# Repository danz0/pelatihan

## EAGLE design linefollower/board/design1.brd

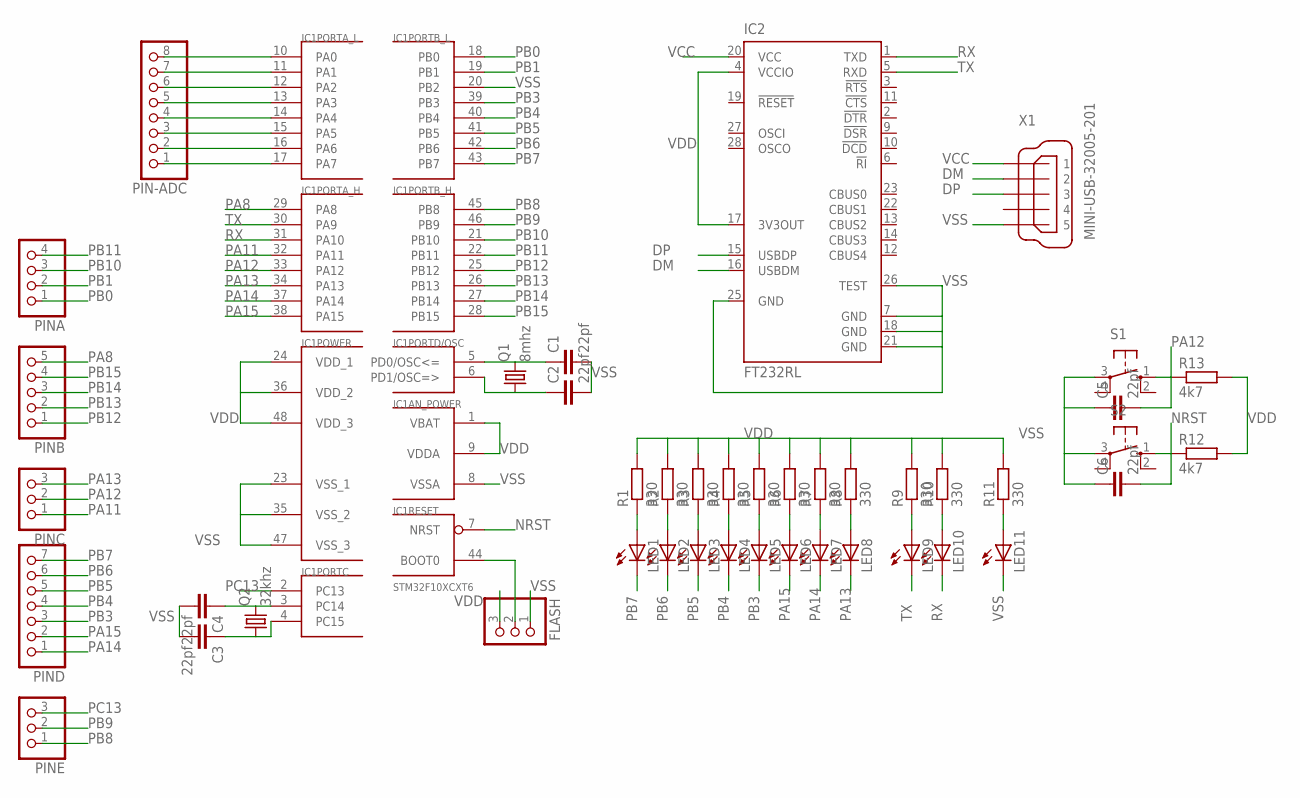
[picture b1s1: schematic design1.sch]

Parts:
C1, C2, C3, C4, C5, C6: 22pf; C1206
FLASH: PINHD-1X3; 1X03
IC1: STM32F10XCXT6; TQFP48
IC2: FT232RL; SSOP28
LED1, LED2, LED3, LED4, LED5, LED6, LED7, LED8, LED9, LED10, LED11: LEDSML1206; SML1206
PIN-ADC: PINHD-1X8; 1X08
PINA: PINHD-1X4; 1X04
PINB: PINHD-1X5; 1X05
PINC: PINHD-1X3; 1X03
PIND: PINHD-1X7; 1X07
PINE: PINHD-1X3; 1X03
Q1: 8mhz; HC49U-V
Q2: 32khz; TC26V
R1, R2, R3, R4, R5, R6, R7, R8, R9, R10, R11: 330; R1206
R12, R13: 4k7; R1206
S1, S2: 10-XX; B3F-10XX
X1: MINI-USB-32005-201; 32005-201

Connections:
ADC0: IC1.10 (PA0), PIN-ADC.8
ADC1: IC1.11 (PA1), PIN-ADC.7
ADC2: IC1.12 (PA2), PIN-ADC.6
ADC3: IC1.13 (PA3), PIN-ADC.5
ADC4: IC1.14 (PA4), PIN-ADC.4
ADC5: IC1.15 (PA5), PIN-ADC.3
ADC6: IC1.16 (PA6), PIN-ADC.2
ADC7: IC1.17 (PA7), PIN-ADC.1
DM: IC2.16 (USBDM), X1.2
DP: IC2.15 (USBDP), X1.3
unnamed: C1.1, IC1.5 (PD0/OSC<=), Q1.2
unnamed: C2.1, IC1.6 (PD1/OSC=>), Q1.1
unnamed: C3.1, IC1.4 (PC15), Q2.1
unnamed: C4.1, IC1.3 (PC14), Q2.2
unnamed: FLASH.2, IC1.44 (BOOT0)
unnamed: LED1.A, R1.1
unnamed: LED2.A, R2.1
unnamed: LED3.A, R3.1
unnamed: LED4.A, R4.1
unnamed: LED5.A, R5.1
unnamed: LED6.A, R6.1
unnamed: LED7.A, R7.1
unnamed: LED8.A, R8.1
unnamed: LED9.A, R9.1
unnamed: LED10.A, R10.1
unnamed: LED11.A, R11.1
NRST: C6.2, IC1.7 (NRST), R12.1, S2.1 (S)
PA8: IC1.29 (PA8), PINB.5
PA11: IC1.32 (PA11), PINC.1
PA12: C5.2, IC1.33 (PA12), PINC.2, R13.1, S1.1 (S)
PA13: IC1.34 (PA13), LED8.C, PINC.3
PA14: IC1.37 (PA14), LED7.C, PIND.1
PA15: IC1.38 (PA15), LED6.C, PIND.2
PB0: IC1.18 (PB0), PINA.1
PB1: IC1.19 (PB1), PINA.2
PB3: IC1.39 (PB3), LED5.C, PIND.3
PB4: IC1.40 (PB4), LED4.C, PIND.4
PB5: IC1.41 (PB5), LED3.C, PIND.5
PB6: IC1.42 (PB6), LED2.C, PIND.6
PB7: IC1.43 (PB7), LED1.C, PIND.7
PB8: IC1.45 (PB8), PINE.1
PB9: IC1.46 (PB9), PINE.2
PB10: IC1.21 (PB10), PINA.3
PB11: IC1.22 (PB11), PINA.4
PB12: IC1.25 (PB12), PINB.1
PB13: IC1.26 (PB13), PINB.2
PB14: IC1.27 (PB14), PINB.3
PB15: IC1.28 (PB15), PINB.4
PC13: IC1.2 (PC13), PINE.3
RX: IC1.31 (PA10), IC2.1 (TXD), LED10.C
TX: IC1.30 (PA9), IC2.5 (RXD), LED9.C
VCC: IC2.20 (VCC), X1.1
VDD: FLASH.3, IC1.1 (VBAT), IC1.9 (VDDA), IC1.24 (VDD_1), IC1.36 (VDD_2), IC1.48 (VDD_3), IC2.4 (VCCIO), IC2.17 (3V3OUT), R1.2, R2.2, R3.2, R4.2, R5.2, R6.2, R7.2, R8.2, R9.2, R10.2, R11.2, R12.2, R13.2; also elsewhere on the board
VSS: C1.2, C2.2, C3.2, C4.2, C5.1, C6.1, FLASH.1, IC1.8 (VSSA), IC1.20 (PB2), IC1.23 (VSS_1), IC1.35 (VSS_2), IC1.47 (VSS_3), IC2.7 (GND), IC2.18 (GND), IC2.21 (GND), IC2.25 (GND), IC2.26 (TEST), LED11.C, S1.3, S2.3, X1.5; also elsewhere on the board

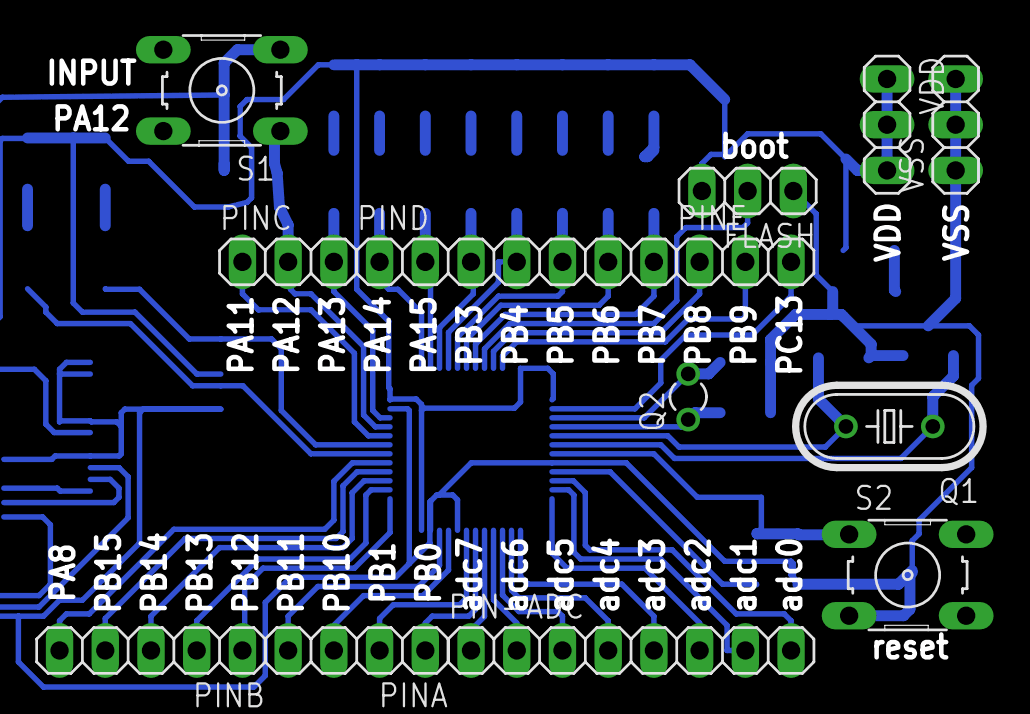
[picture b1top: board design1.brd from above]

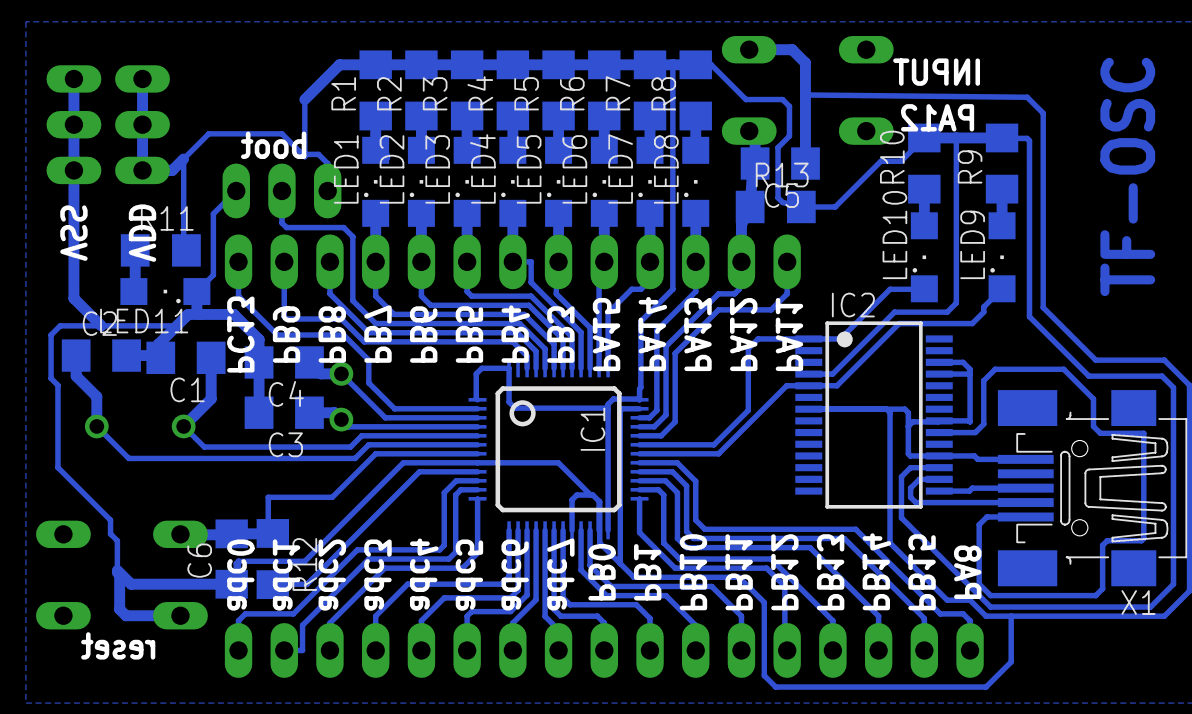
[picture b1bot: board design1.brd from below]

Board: 2 copper layers, 46 parts (33 on the bottom side), 54 nets.

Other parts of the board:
VDD: 1X03
VSS: 1X03

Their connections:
VDD: VDD.1, VDD.2, VDD.3; also elsewhere on the board
VSS: VSS.1, VSS.2, VSS.3; also elsewhere on the board

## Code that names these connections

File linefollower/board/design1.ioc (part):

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Mcu.Name=STM32F100C(4-6)Tx
Mcu.Package=LQFP48
PA0-WKUP.Mode=IN0
PA0-WKUP.Signal=ADC1_IN0
PA1.Mode=IN1
PA1.Signal=ADC1_IN1
PA10.Mode=Asynchronous
PA10.Signal=USART1_RX
PA2.Mode=IN2
PA2.Signal=ADC1_IN2
PA3.Mode=IN3
PA3.Signal=ADC1_IN3
PA4.Mode=IN4
PA4.Signal=ADC1_IN4
PA5.Mode=IN5
PA5.Signal=ADC1_IN5
PA6.Mode=IN6
PA6.Signal=ADC1_IN6
PA7.Mode=IN7
PA7.Signal=ADC1_IN7
PA9.Mode=Asynchronous
PA9.Signal=USART1_TX
PB2.Mode=Event-Out
PB2.Signal=CORTEX_EVENT_OUT
PC14-OSC32_IN.Mode=LSE-External-Oscillator
PC14-OSC32_IN.Signal=SYS_OSC32_IN
PC15-OSC32_OUT.Mode=LSE-External-Oscillator
PC15-OSC32_OUT.Signal=SYS_OSC32_OUT
PD0-OSC_IN.Mode=HSE-External-Oscillator
PD0-OSC_IN.Signal=SYS_OSC_IN
PD1-OSC_OUT.Mode=HSE-External-Oscillator
PD1-OSC_OUT.Signal=SYS_OSC_OUT

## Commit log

2014-11-29 revisi board
2014-12-04 progress modul
2014-12-05 progress modul (yulia)
2014-12-05 Progres yulia
2014-12-26 ChibiOS
2014-12-26 list paket
2014-12-27 materi qt
2014-12-28 modul jadi
2014-12-28 materi development
